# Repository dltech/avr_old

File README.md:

# avr_old
 peripherial libs for atmega/attiny mcu

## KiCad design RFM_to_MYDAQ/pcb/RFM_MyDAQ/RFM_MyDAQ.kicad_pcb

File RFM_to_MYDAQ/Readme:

Подключение RFM69 к модулю MYDAQ, структура проекта
*pcb - схема и плата, что подключается к блоку
*labview - код для работы с модулем и приема данных с этого модуля для станциии NI PXI
*calc_reg_values - ПО для рассчета регистров RFM, данные оттуда копируются в ПО labview

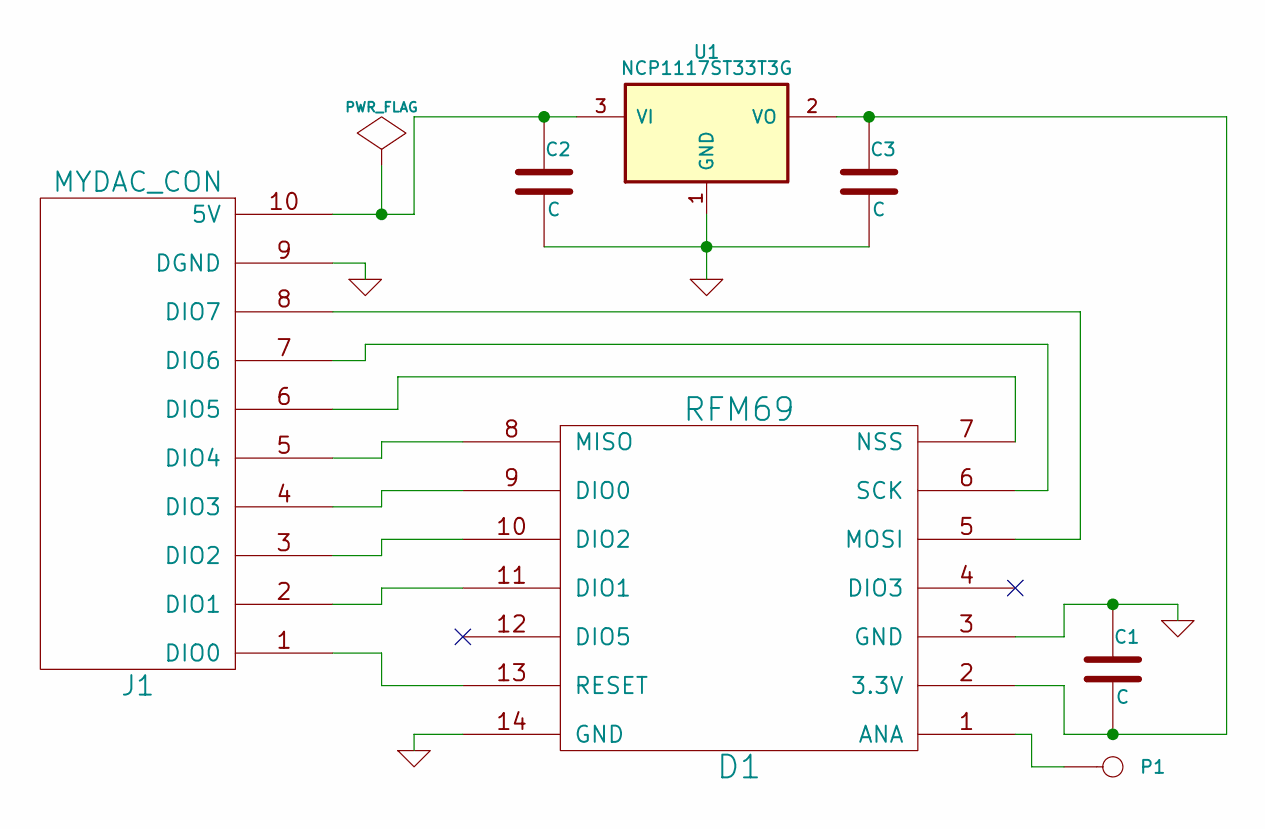
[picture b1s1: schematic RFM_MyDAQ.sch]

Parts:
C1, C2, C3: C
D1: RFM69
J1: MYDAC_CON
P1: CONN_1
U1: NCP1117ST33T3G

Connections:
GND: C1.1, C2.2, C3.2, D1.3 (GND), D1.14 (GND), J1.9 (DGND), U1.1 (GND)
unnamed: D1.5 (MOSI), J1.8 (DIO7)
unnamed: D1.8 (MISO), J1.5 (DIO4)
unnamed: D1.13 (RESET), J1.1 (DIO0)
unnamed: D1.11 (DIO1), J1.2 (DIO1)
unnamed: D1.10 (DIO2), J1.3 (DIO2)
unnamed: D1.9 (DIO0), J1.4 (DIO3)
unnamed: D1.7 (NSS), J1.6 (DIO5)
unnamed: D1.1 (ANA), P1.1
unnamed: D1.6 (SCK), J1.7 (DIO6)
unnamed: C1.2, C3.1, D1.2 (3.3V), U1.2 (VO)
unnamed: C2.1, J1.10 (5V), U1.3 (VI)

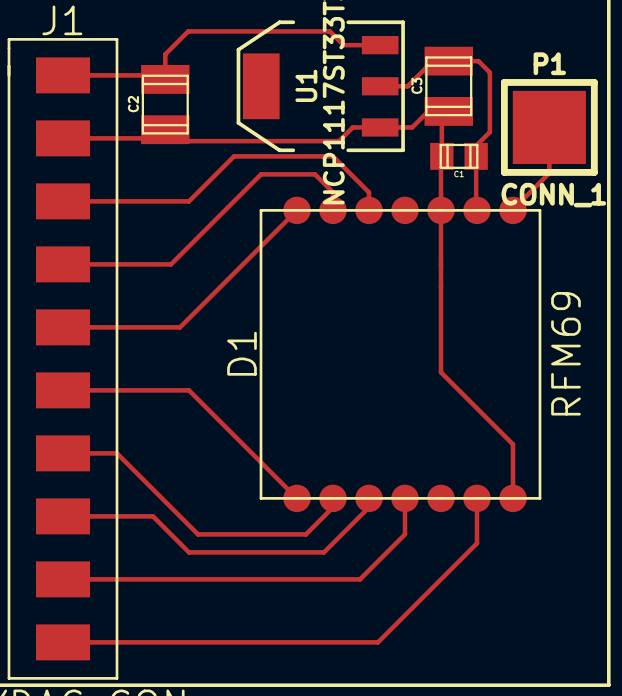
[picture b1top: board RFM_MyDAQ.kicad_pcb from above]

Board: 2 copper layers, 7 parts (0 on the bottom side), 12 nets.

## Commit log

2021-06-12 библиотечки
2021-08-29 гспи не откоменченное
2021-08-29 all other code
2021-08-29 nashel
